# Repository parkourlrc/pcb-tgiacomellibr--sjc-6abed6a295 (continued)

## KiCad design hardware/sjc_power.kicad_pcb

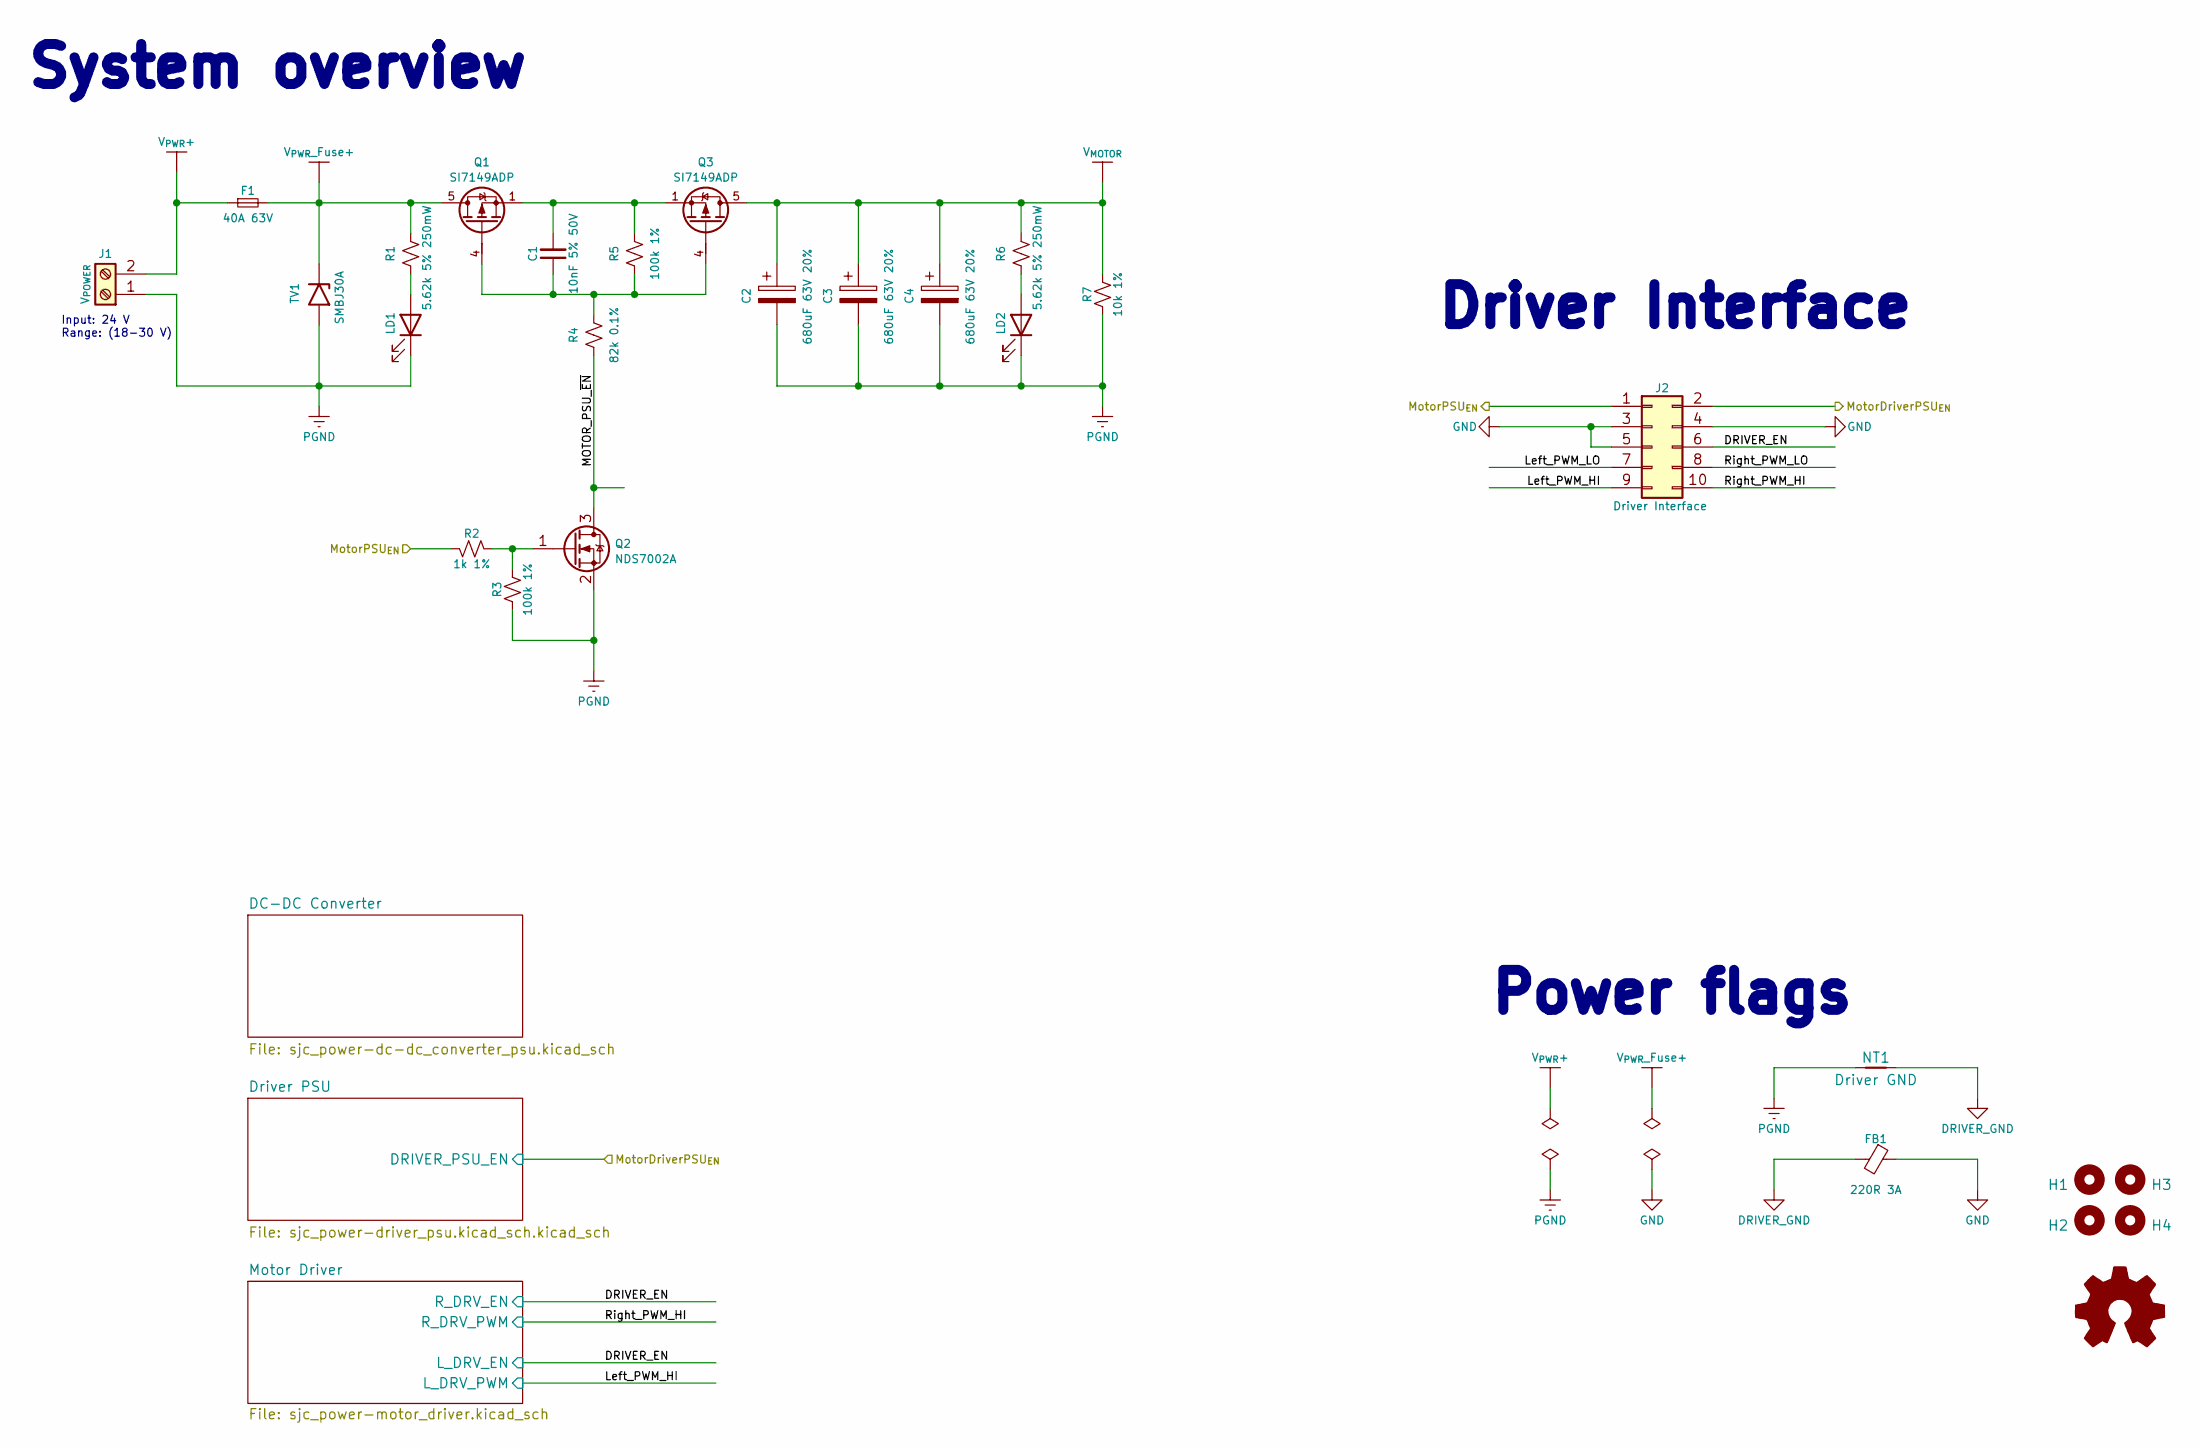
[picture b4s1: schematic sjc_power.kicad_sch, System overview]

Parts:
C1: 10nF 5% 50V; C_0603_1608Metric; JLCPCB Part # C389113
C2, C3, C4: 680uF 63V 20%; CP_Elec_18x17.5; JLCPCB Part # C249956
F1: 40A 63V; Fuse_2410_6125Metric_CB61F; JLCPCB Part # C3166275
FB1: 220R 3A; L_0805_2012Metric_Pad1.05x1.20mm_HandSolder; JLCPCB Part # C76818
H1, H2, H3, H4: MountingHole; MountingHole_3.2mm_M3_ISO7380
J1: V_{POWER}; AMASS_XT60PW-F_1x02_P7.20mm_Horizontal; JLCPCB Part # C428722
J2: Driver Interface; PinHeader_2x05_P2.54mm_Vertical; JLCPCB Part # C225520
LD1, LD2: 1.8V @ 5mA; LED_0603_1608Metric_Pad1.05x0.95mm_HandSolder; JLCPCB Part # C165982
NT1: Driver GND; NetTie-2_SMD_Pad2.0mm
Q1, Q3: SI7149ADP; PowerPAK_SO-8_Single; JLCPCB Part # C554002
Q2: NDS7002A; SOT-23; JLCPCB Part # C74715
R1, R6: 5.62k 5% 250mW; R_0805_2012Metric_Pad1.20x1.40mm_HandSolder; JLCPCB Part # C425493
R2: 1k 1%; R_0603_1608Metric; JLCPCB Part # C22548
R3, R5: 100k 1%; R_0603_1608Metric; JLCPCB Part # C14675
R4: 82k 0.1%; R_0603_1608Metric; JLCPCB Part # C728598
R7: 10k 1%; R_0603_1608Metric; JLCPCB Part # C98220
SYM1: Logo_Open_Hardware_Small; OSHW-Logo2_9.8x8mm_SilkScreen
TV1: SMBJ30A; D_SMB_Handsoldering; JLCPCB Part # C83851

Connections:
/DRIVER_EN: J2.6; also elsewhere on the board
/Left_PWM_HI: J2.9; also elsewhere on the board
/Left_PWM_LO: J2.7
/MOTOR_PSU_~EN: Q2.3 (D), R4.1
/MotorDriverPSU_{EN}: J2.2; also elsewhere on the board
/MotorPSU_{EN}: J2.1, R2.2
/Right_PWM_HI: J2.10; also elsewhere on the board
/Right_PWM_LO: J2.8
DRIVER_GND: FB1.2, NT1.2; also elsewhere on the board
GND: FB1.1, J2.3, J2.4, J2.5
unnamed: C1.2, Q1.1 (S), Q1.2 (S), Q1.3 (S), Q3.1 (S), Q3.2 (S), Q3.3 (S), R5.2
unnamed: LD1.2 (A), R1.1
unnamed: LD2.2 (A), R6.1
unnamed: C1.1, Q1.4 (G), Q3.4 (G), R4.2, R5.1
unnamed: Q2.1 (G), R2.1, R3.2
PGND: C2.2, C3.2, C4.2, J1.1, LD1.1 (K), LD2.1 (K), NT1.1, Q2.2 (S), R3.1, R7.1, TV1.2 (A); also elsewhere on the board
V_{MOTOR}: C2.1, C3.1, C4.1, Q3.5 (D), R6.2, R7.2; also elsewhere on the board
V_{PWR}+: F1.1, J1.2
V_{PWR}_Fuse+: F1.2, Q1.5 (D), R1.2, TV1.1 (K); also elsewhere on the board

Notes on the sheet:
Power flags
Driver Interface
System overview
Input: 24 V Range: (18-30 V)

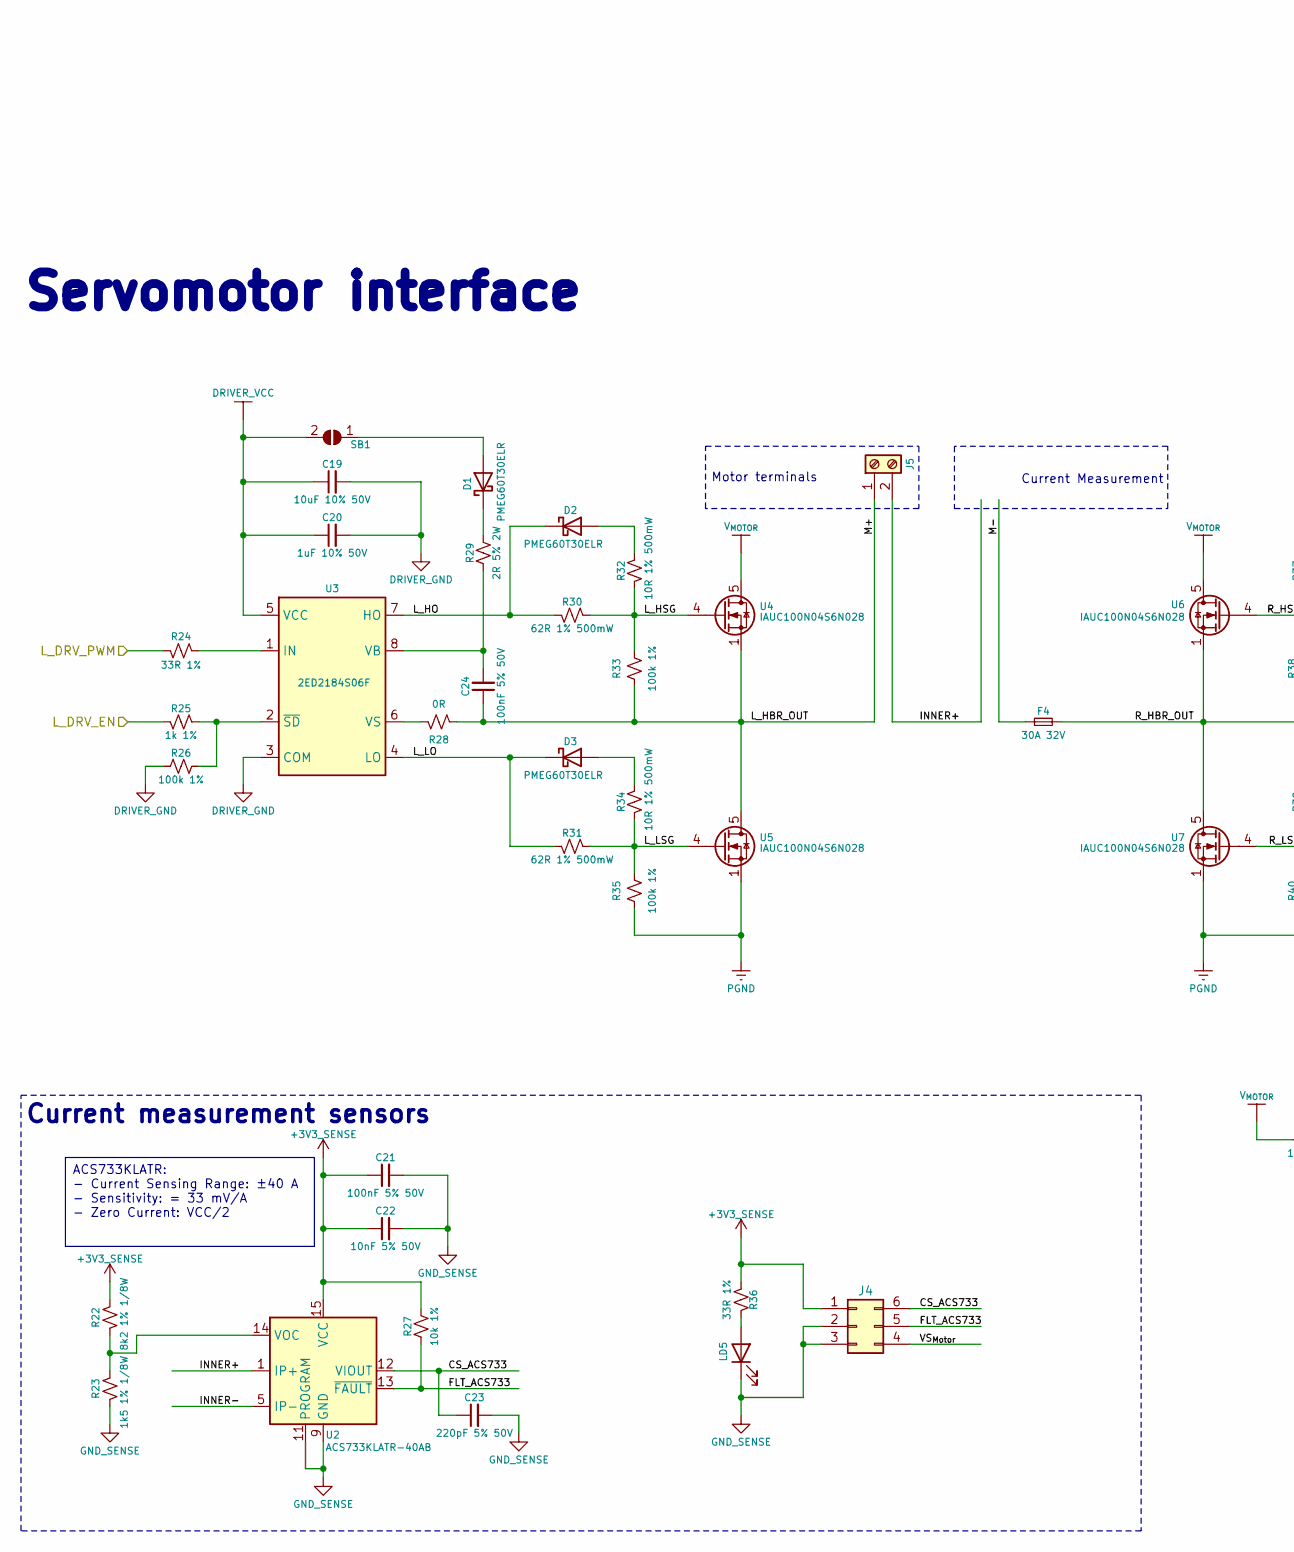
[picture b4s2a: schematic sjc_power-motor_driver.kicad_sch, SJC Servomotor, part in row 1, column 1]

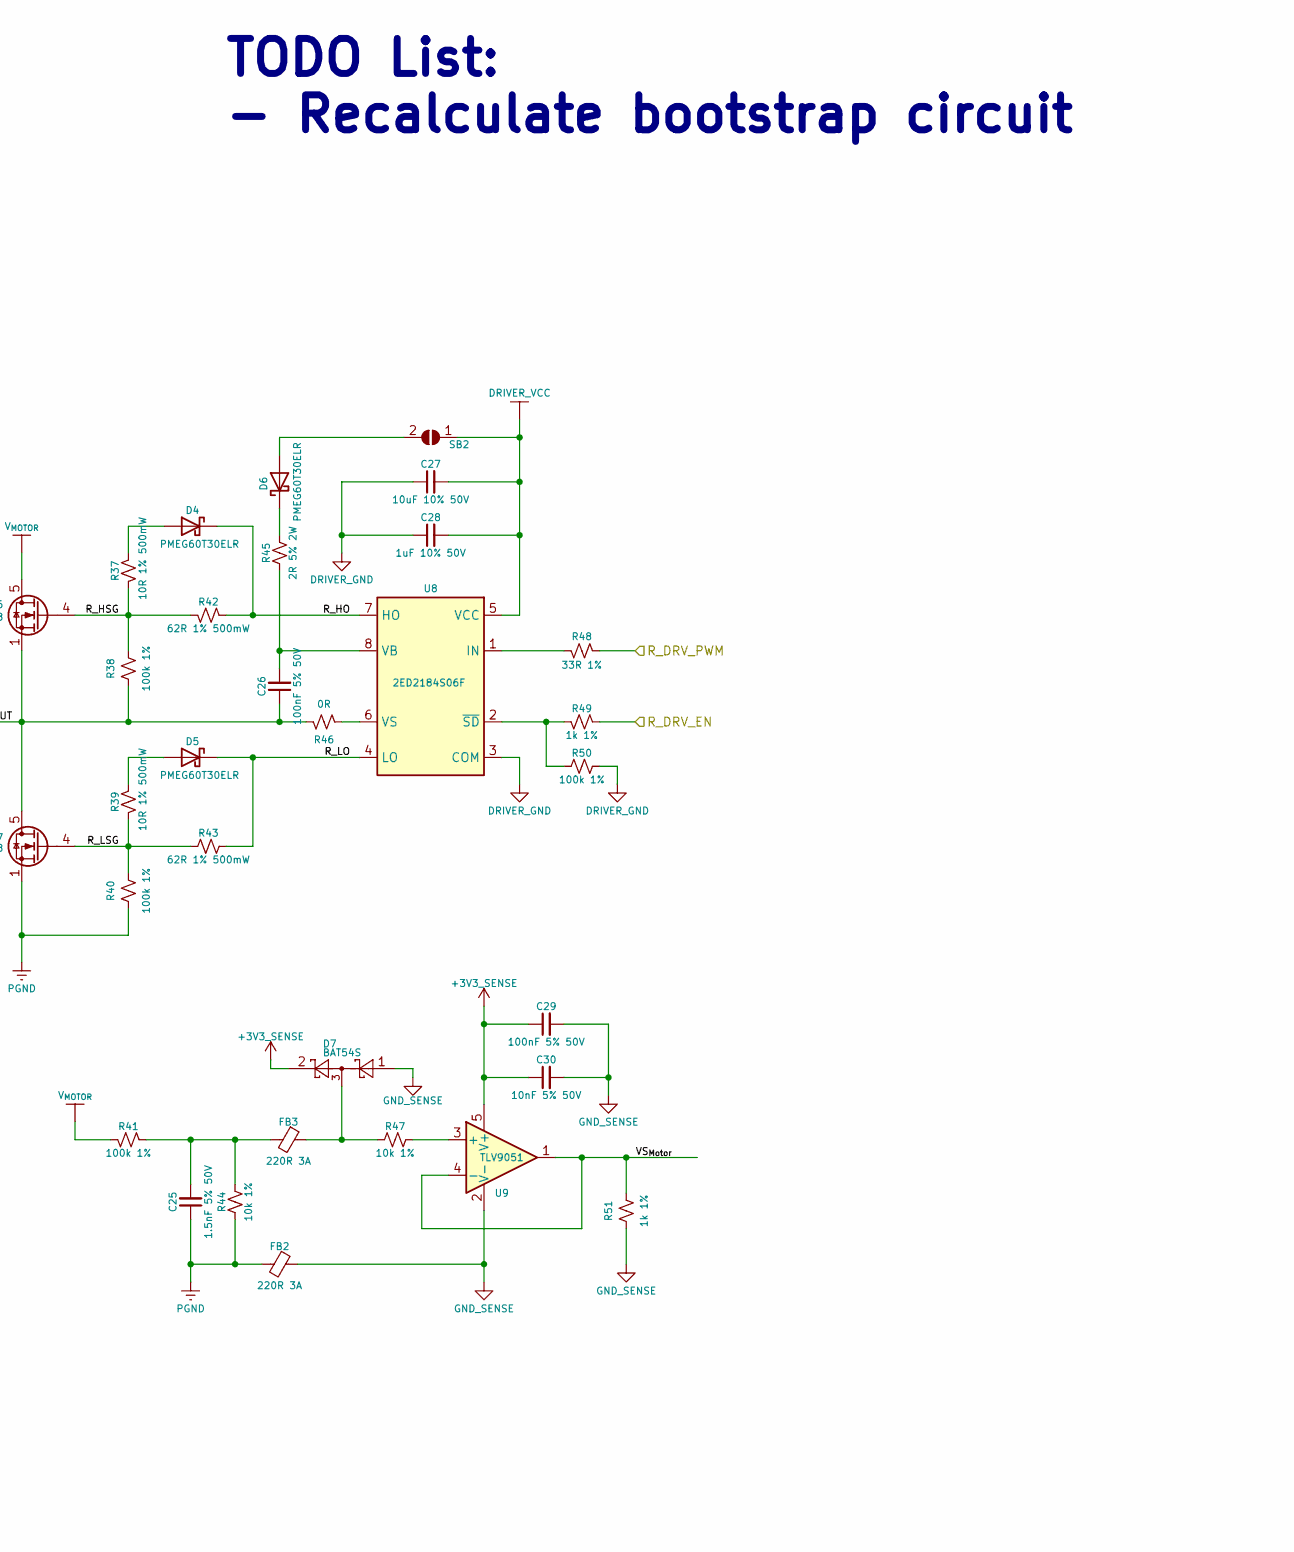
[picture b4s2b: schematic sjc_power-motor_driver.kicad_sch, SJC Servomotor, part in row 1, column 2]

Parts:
C19, C27: 10uF 10% 50V; C_1206_3216Metric; JLCPCB Part # C13585
C20, C28: 1uF 10% 50V; C_1206_3216Metric; JLCPCB Part # C1848
C21, C29: 100nF 5% 50V; C_0603_1608Metric; JLCPCB Part # C91183
C22, C30: 10nF 5% 50V; C_0603_1608Metric; JLCPCB Part # C389113
C23: 220pF 5% 50V; C_0402_1005Metric_Pad0.74x0.62mm_HandSolder; JLCPCB Part # C301973
C24, C26: 100nF 5% 50V; C_0805_2012Metric_Pad1.18x1.45mm_HandSolder; JLCPCB Part # C111492
C25: 1.5nF 5% 50V; C_0603_1608Metric; JLCPCB Part # C107039
D1, D2, D3, D4, D5, D6: PMEG60T30ELR; D_SOD-123F; JLCPCB Part # C2938304
D7: BAT54S; SOT-23; JLCPCB Part # C19726
F4: 30A 32V; Fuse_1206_3216Metric_Pad1.42x1.75mm_HandSolder; JLCPCB Part # C2925002
FB2, FB3: 220R 3A; L_0805_2012Metric_Pad1.05x1.20mm_HandSolder; JLCPCB Part # C76818
J4: Current Sensor; PinHeader_2x03_P2.54mm_Vertical
J5: Motor; AMASS_XT60PW-F_1x02_P7.20mm_Horizontal; JLCPCB Part # C428722
LD5: 1.8V @ 5mA; LED_0603_1608Metric_Pad1.05x0.95mm_HandSolder; JLCPCB Part # C165982
R22: 8k2 1% 1/8W; R_0805_2012Metric_Pad1.20x1.40mm_HandSolder; JLCPCB Part # C114545
R23: 1k5 1% 1/8W; R_0805_2012Metric_Pad1.20x1.40mm_HandSolder; JLCPCB Part # C163950
R24, R36, R48: 33R 1%; R_0603_1608Metric; JLCPCB Part # C108661
R25, R49, R51: 1k 1%; R_0603_1608Metric; JLCPCB Part # C22548
R26, R33, R35, R38, R40, R41, R50: 100k 1%; R_0603_1608Metric; JLCPCB Part # C14675
R27, R44, R47: 10k 1%; R_0603_1608Metric; JLCPCB Part # C98220
R28, R46: 0R; R_0603_1608Metric; JLCPCB Part # C103196
R29, R45: 2R 5% 2W; R_2512_6332Metric_Pad1.40x3.35mm_HandSolder; JLCPCB Part # C91926
R30, R31, R42, R43: 62R 1% 500mW; R_1210_3225Metric_Pad1.30x2.65mm_HandSolder; JLCPCB Part # C966313
R32, R34, R37, R39: 10R 1% 500mW; R_1210_3225Metric_Pad1.30x2.65mm_HandSolder; JLCPCB Part # C44451
SB1, SB2: SolderJumper-2_P1.3mm_Open_RoundedPad1.0x1.5mm
U2: ACS733KLATR-40AB; SOIC-16W_7.5x10.3mm_P1.27mm; JLCPCB Part # C459339
U3, U8: 2ED2184S06F; Infineon_PG-DSO-8-24_4x5mm; JLCPCB Part # C1848362
U4, U5, U6, U7: IAUC100N04S6N028; Infineon_PG-TDSON-8_6.15x5.15mm; JLCPCB Part # C3288826
U9: TLV9051; SOT-23-5; JLCPCB Part # C1849429

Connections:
+3V3_SENSE: C21.1, C22.1, C29.1, C30.1, D7.2, J4.1, R22.1, R27.2, R36.2, U2.15 (VCC), U2.16 (VCC), U9.5 (V+)
/DRIVER_EN: R25.2, R49.1; also elsewhere on the board
/Left_PWM_HI: R24.2; also elsewhere on the board
/Motor Driver/CS_ACS733: C23.1, J4.6, U2.12 (VIOUT)
/Motor Driver/FLT_ACS733: J4.5, R27.1, U2.13 (~FAULT)
/Motor Driver/INNER+: J5.2, U2.1 (IP+), U2.2 (IP+), U2.3 (IP+), U2.4 (IP+)
/Motor Driver/INNER-: U2.5 (IP-), U2.6 (IP-), U2.7 (IP-), U2.8 (IP-)
/Motor Driver/L_HBR_OUT: C24.1, J5.1, R28.2, R33.1, U4.1 (S), U4.2 (S), U4.3 (S), U5.5 (D)
/Motor Driver/L_HO: D2.1 (K), R30.2, U3.7 (HO)
/Motor Driver/L_HSG: R30.1, R32.2, R33.2, U4.4 (G)
/Motor Driver/L_LO: D3.1 (K), R31.2, U3.4 (LO)
/Motor Driver/L_LSG: R31.1, R34.2, R35.2, U5.4 (G)
/Motor Driver/M-: F4.1
/Motor Driver/R_HBR_OUT: C26.1, F4.2, R38.1, R46.1, U6.1 (S), U6.2 (S), U6.3 (S), U7.5 (D)
/Motor Driver/R_HO: D4.1 (K), R42.1, U8.7 (HO)
/Motor Driver/R_HSG: R37.2, R38.2, R42.2, U6.4 (G)
/Motor Driver/R_LO: D5.1 (K), R43.2, U8.4 (LO)
/Motor Driver/R_LSG: R39.2, R40.2, R43.1, U7.4 (G)
/Motor Driver/VS_{Motor}: J4.4, R51.2, U9.1, U9.4 (-)
/Right_PWM_HI: R48.1; also elsewhere on the board
DRIVER_GND: C19.2, C20.2, C27.1, C28.1, R26.1, R50.2, U3.3 (COM), U8.3 (COM); also elsewhere on the board
DRIVER_VCC: C19.1, C20.1, C27.2, C28.2, SB1.2 (B), SB2.1 (A), U3.5 (VCC), U8.5 (VCC); also elsewhere on the board
GND_SENSE: C21.2, C22.2, C23.2, C29.2, C30.2, D7.1, FB2.1, J4.2, J4.3, LD5.1 (K), R23.2, R51.1, U2.9 (GND), U2.10 (GND), U2.11 (PROGRAM), U9.2 (V-)
unnamed: C25.2, FB3.2, R41.1, R44.2
unnamed: D1.2 (A), SB1.1 (A)
unnamed: D1.1 (K), R29.2
unnamed: D2.2 (A), R32.1
unnamed: D3.2 (A), R34.1
unnamed: D4.2 (A), R37.1
unnamed: D5.2 (A), R39.1
unnamed: D6.2 (A), SB2.2 (B)
unnamed: D6.1 (K), R45.2
unnamed: D7.3, FB3.1, R47.1
unnamed: LD5.2 (A), R36.1
unnamed: R22.2, R23.1, U2.14 (VOC)
unnamed: R24.1, U3.1 (IN)
unnamed: C24.2, R29.1, U3.8 (VB)
unnamed: R28.1, U3.6 (VS)
unnamed: R25.1, R26.2, U3.2 (~SD)
unnamed: R48.2, U8.1 (IN)
unnamed: C26.2, R45.1, U8.8 (VB)
unnamed: R46.2, U8.6 (VS)
unnamed: R49.2, R50.1, U8.2 (~SD)
unnamed: R47.2, U9.3 (+)
PGND: C25.1, FB2.2, R35.1, R40.1, R44.1, U5.1 (S), U5.2 (S), U5.3 (S), U7.1 (S), U7.2 (S), U7.3 (S); also elsewhere on the board
V_{MOTOR}: R41.2, U4.5 (D), U6.5 (D); also elsewhere on the board

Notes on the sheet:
Current measurement sensors
Current Measurement
Servomotor interface
Motor terminals
TODO List: - Recalculate bootstrap circuit
ACS733KLATR: - Current Sensing Range: ±40 A - Sensitivity: = 33 mV/A - Zero Current: VCC/2

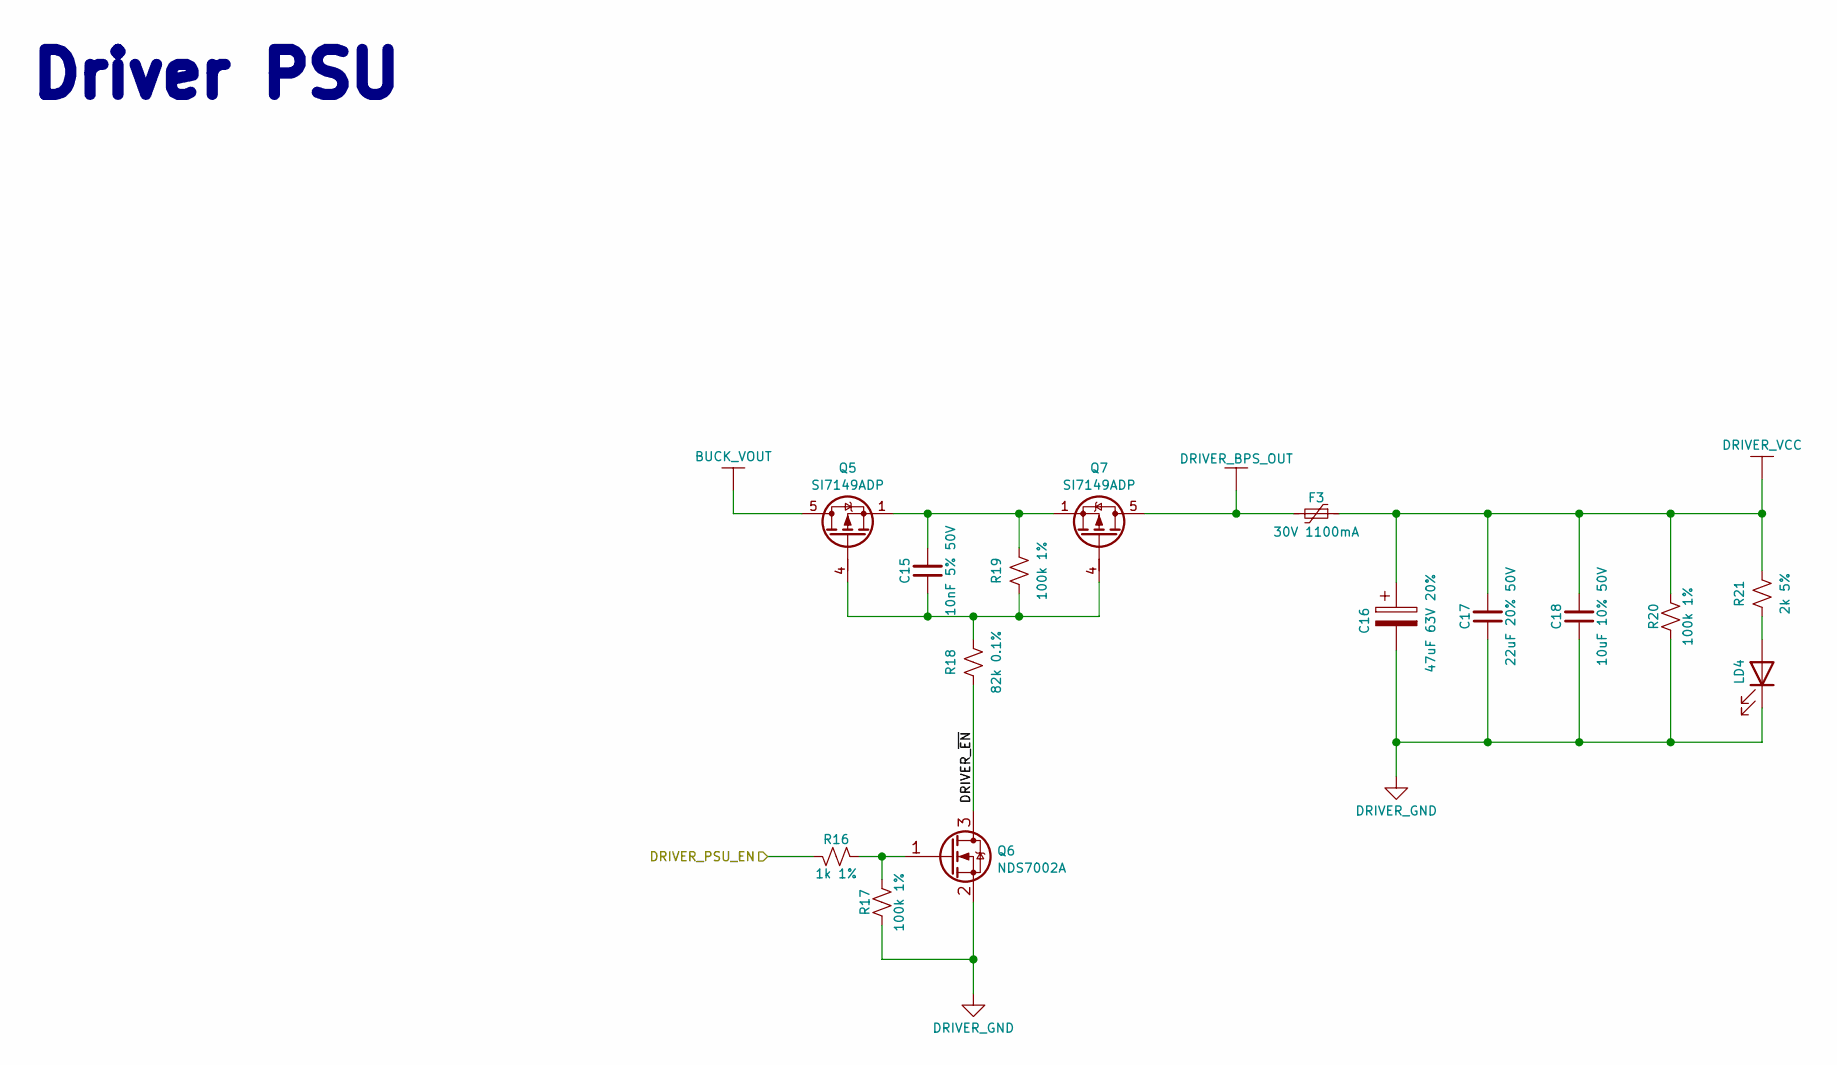
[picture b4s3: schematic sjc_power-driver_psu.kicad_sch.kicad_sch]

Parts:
C15: 10nF 5% 50V; C_0603_1608Metric; JLCPCB Part # C389113
C16: 47uF 63V 20%; CP_Elec_8x10.5; JLCPCB Part # C116428
C17: 22uF 20% 50V; C_2220_5750Metric; JLCPCB Part # C2178233
C18: 10uF 10% 50V; C_1206_3216Metric; JLCPCB Part # C13585
F3: 30V 1100mA; Fuse_1206_3216Metric_Pad1.42x1.75mm_HandSolder; JLCPCB Part # C7542963
LD4: 1.8V @ 5mA; LED_0603_1608Metric_Pad1.05x0.95mm_HandSolder; JLCPCB Part # C165982
Q5, Q7: SI7149ADP; PowerPAK_SO-8_Single; JLCPCB Part # C554002
Q6: NDS7002A; SOT-23; JLCPCB Part # C74715
R16: 1k 1%; R_0603_1608Metric; JLCPCB Part # C22548
R17, R19, R20: 100k 1%; R_0603_1608Metric; JLCPCB Part # C14675
R18: 82k 0.1%; R_0603_1608Metric; JLCPCB Part # C728598
R21: 2k 5%; R_0603_1608Metric; JLCPCB Part # C103396

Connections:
/Driver PSU/DRIVER_~EN: Q6.3 (D), R18.1
/MotorDriverPSU_{EN}: R16.2; also elsewhere on the board
BUCK_VOUT: Q5.5 (D); also elsewhere on the board
DRIVER_BPS_OUT: F3.2, Q7.5 (D)
DRIVER_GND: C16.2, C17.1, C18.1, LD4.1 (K), Q6.2 (S), R17.1, R20.1; also elsewhere on the board
DRIVER_VCC: C16.1, C17.2, C18.2, F3.1, R20.2, R21.2; also elsewhere on the board
unnamed: C15.2, Q5.1 (S), Q5.2 (S), Q5.3 (S), Q7.1 (S), Q7.2 (S), Q7.3 (S), R19.2
unnamed: LD4.2 (A), R21.1
unnamed: C15.1, Q5.4 (G), Q7.4 (G), R18.2, R19.1
unnamed: Q6.1 (G), R16.1, R17.2

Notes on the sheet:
Driver PSU

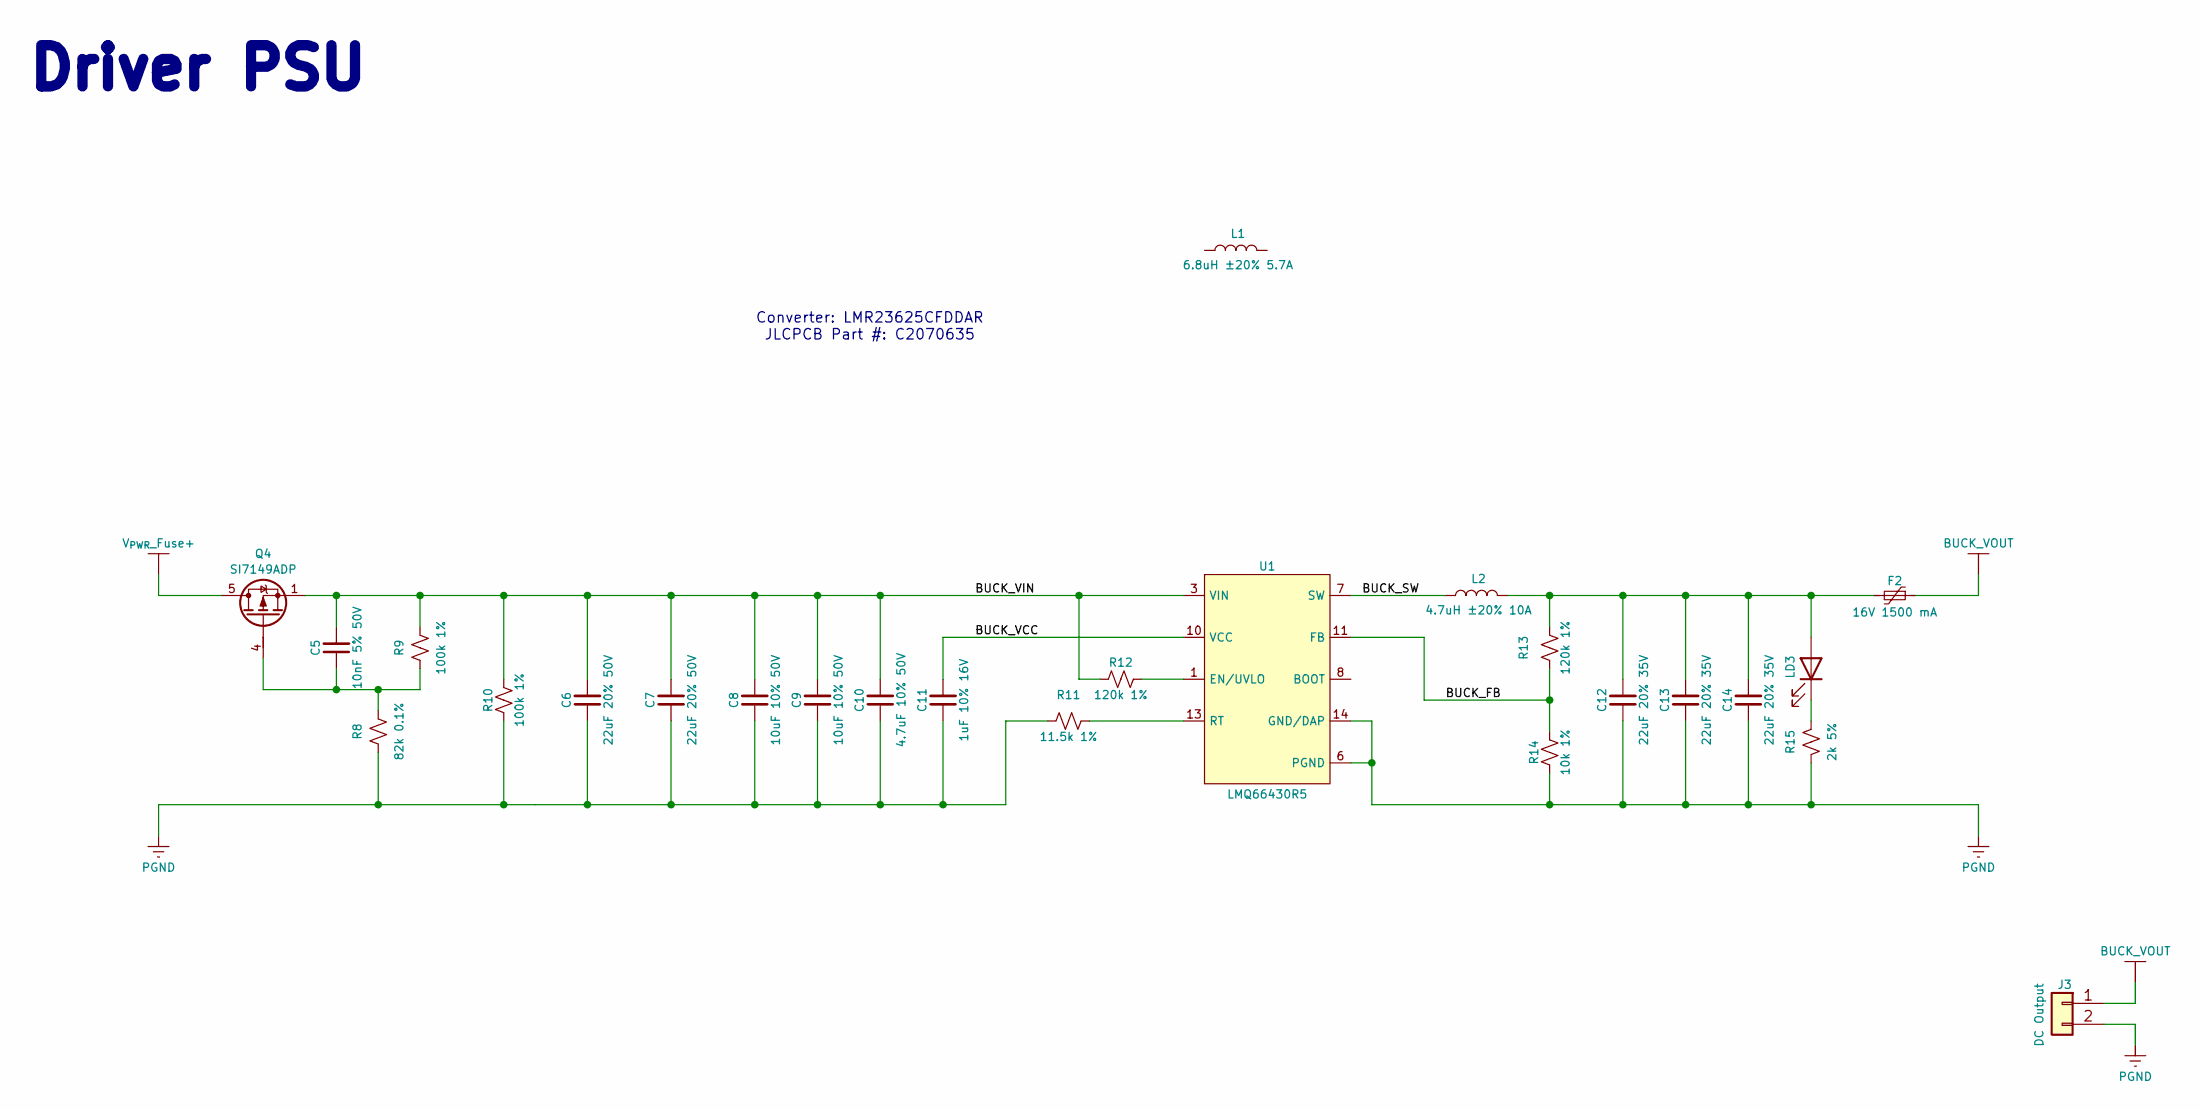
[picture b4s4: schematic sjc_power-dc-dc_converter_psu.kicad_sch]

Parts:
C5: 10nF 5% 50V; C_0603_1608Metric; JLCPCB Part # C389113
C6, C7: 22uF 20% 50V; C_2220_5750Metric; JLCPCB Part # C2178233
C8, C9: 10uF 10% 50V; C_1206_3216Metric; JLCPCB Part # C13585
C10: 4.7uF 10% 50V; C_1206_3216Metric_Pad1.33x1.80mm_HandSolder; JLCPCB Part # C77096
C11: 1uF 10% 16V; C_0603_1608Metric_Pad1.08x0.95mm_HandSolder; JLCPCB Part # C92759
C12, C13, C14: 22uF 20% 35V; C_0805_2012Metric_Pad1.18x1.45mm_HandSolder; JLCPCB Part # C338080
F2: 16V 1500 mA; Fuse_1206_3216Metric_Pad1.42x1.75mm_HandSolder; JLCPCB Part # C22379952
J3: DC Output; TerminalBlock_Phoenix_MKDS-3-2-5.08_1x02_P5.08mm_Horizontal; JLCPCB Part # C2915639
L1: 6.8uH ±20% 5.7A; L_Vishay_IHLP-3232DZ-01; JLCPCB Part # C2051933
L2: 4.7uH ±20% 10A; L_Vishay_IHLP-5050; JLCPCB Part # C845092
LD3: 1.8V @ 5mA; LED_0603_1608Metric_Pad1.05x0.95mm_HandSolder; JLCPCB Part # C165982
Q4: SI7149ADP; PowerPAK_SO-8_Single; JLCPCB Part # C554002
R8: 82k 0.1%; R_0603_1608Metric; JLCPCB Part # C728598
R9, R10: 100k 1%; R_0603_1608Metric; JLCPCB Part # C14675
R11: 11.5k 1%; R_0603_1608Metric_Pad0.98x0.95mm_HandSolder; JLCPCB Part # C100728
R12, R13: 120k 1%; R_0603_1608Metric_Pad0.98x0.95mm_HandSolder; JLCPCB Part # C114607
R14: 10k 1%; R_0603_1608Metric; JLCPCB Part # C98220
R15: 2k 5%; R_0603_1608Metric; JLCPCB Part # C103396
U1: LMQ66430R5; VQFN-15-1EP_2.6x2.6mm_P0.5mm_EP1.0x1.0mm; JLCPCB Part # C22440565

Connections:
/DC-DC Converter/BUCK_FB: R13.1, R14.2, U1.11 (FB)
/DC-DC Converter/BUCK_SW: L2.1, U1.7 (SW)
/DC-DC Converter/BUCK_VCC: C11.2, U1.10 (VCC)
/DC-DC Converter/BUCK_VIN: C5.2, C6.2, C7.2, C8.2, C9.2, C10.2, Q4.1 (S), Q4.2 (S), Q4.3 (S), R9.2, R10.2, R12.1, U1.3 (VIN)
BUCK_VOUT: F2.1, J3.1; also elsewhere on the board
unnamed: C12.2, C13.2, C14.2, F2.2, L2.2, LD3.2 (A), R13.2
unnamed: LD3.1 (K), R15.1
unnamed: C5.1, Q4.4 (G), R8.2, R9.1
unnamed: R12.2, U1.1 (EN/UVLO)
unnamed: U1.2 (NC), U1.4 (NC), U1.5 (NC), U1.9 (NC), U1.12 (NC)
unnamed: R11.2, U1.13 (RT)
PGND: C6.1, C7.1, C8.1, C9.1, C10.1, C11.1, C12.1, C13.1, C14.1, J3.2, R8.1, R10.1, R11.1, R14.1, R15.2, U1.6 (PGND), U1.14 (GND/DAP); also elsewhere on the board
V_{PWR}_Fuse+: Q4.5 (D); also elsewhere on the board

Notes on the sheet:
Driver PSU
Converter: LMR23625CFDDAR JLCPCB Part #: C2070635

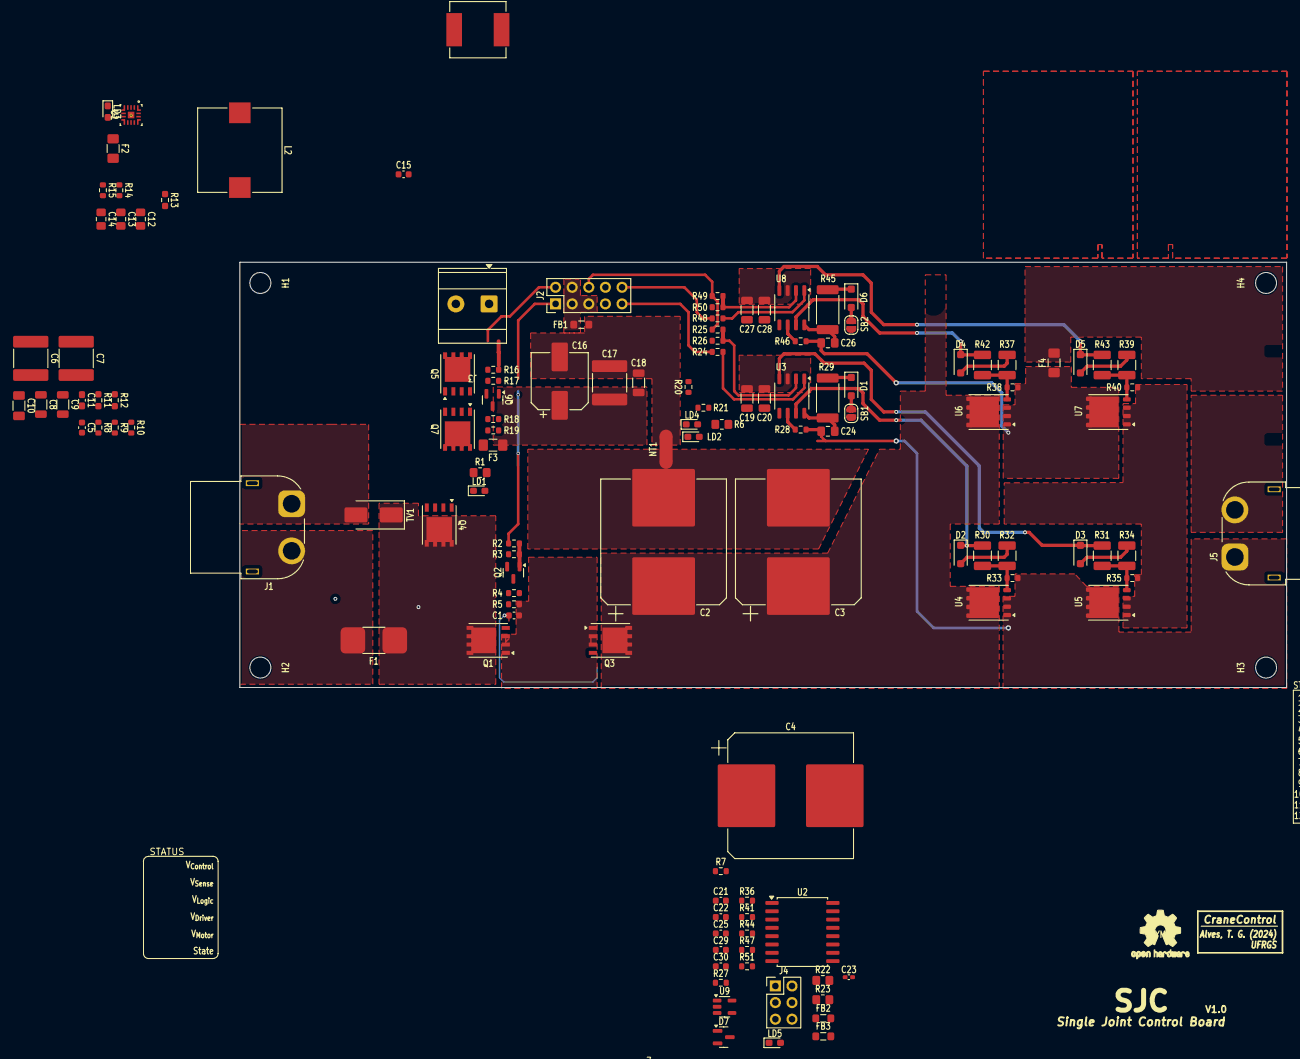
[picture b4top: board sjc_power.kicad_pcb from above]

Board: 4 copper layers, 160.0 x 65.0 mm, 132 parts (0 on the bottom side), 73 nets.

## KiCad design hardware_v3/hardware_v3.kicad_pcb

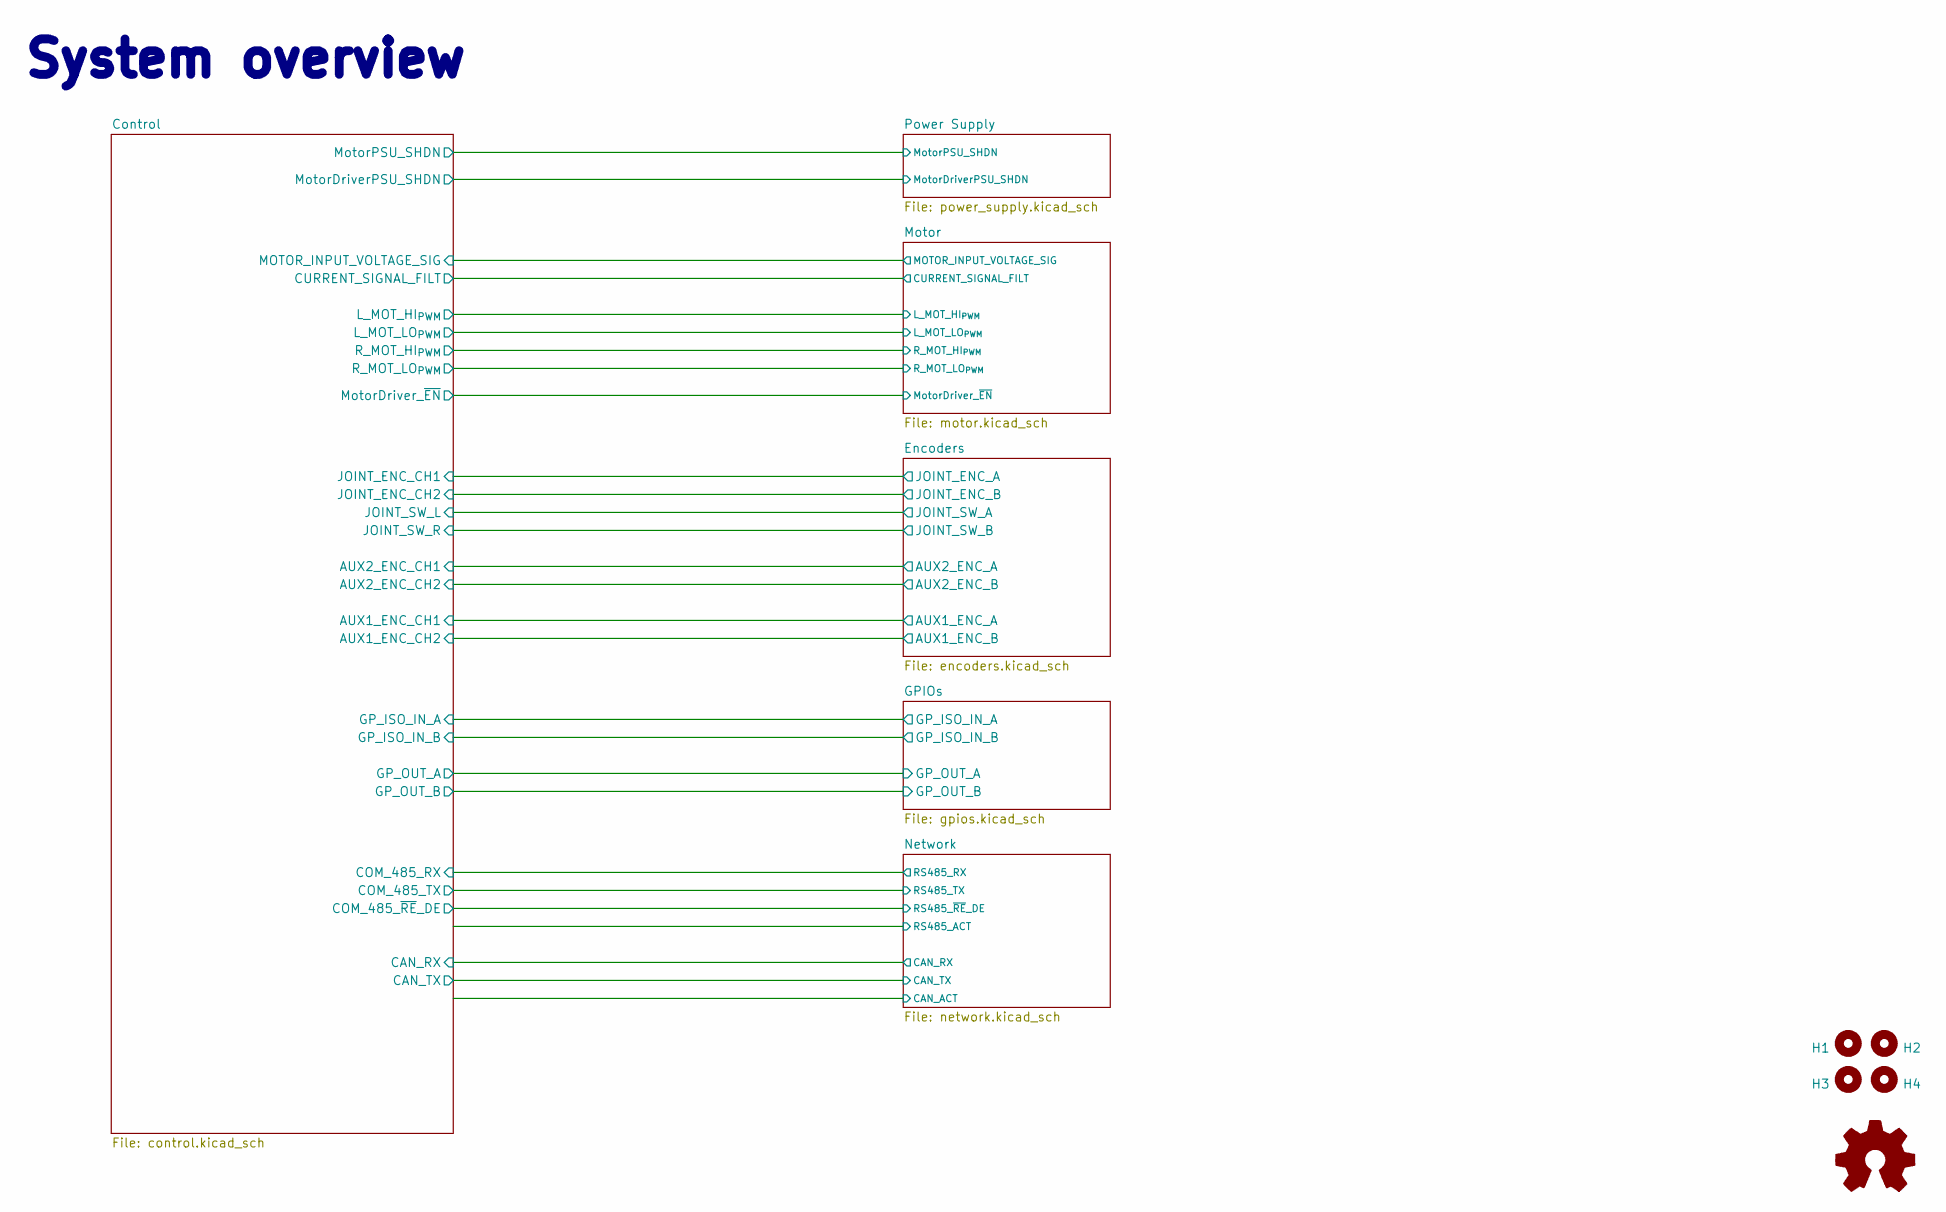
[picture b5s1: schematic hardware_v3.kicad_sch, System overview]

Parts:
H1, H2, H3, H4: MountingHole; MountingHole_3.2mm_M3_ISO7380
SYM1: Logo_Open_Hardware_Small; OSHW-Logo2_9.8x8mm_SilkScreen

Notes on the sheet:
System overview
